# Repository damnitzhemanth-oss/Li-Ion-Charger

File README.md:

2# Li-Ion-Charger
Custom lithium ion charger that is small and does not blow up.

**The Problem** : In Indian market especially, TP4050 is available to charge lithium ion battery, but it sucks as it slowly damages the cell. But there are bigger alternatives which safely charge it. Buy those are bulky. This *Custom Li Ion charger* solves that.

# Features

1. 2A+ charging so you can charge with normal chargers.
2. Type C only.
3. Status LEDs (Red 🍒 - Charging, Green 🍏 - Charged)
4. Over Current protection with Mosfets

# BOM

| Ref | Value / Part | Description | JLCPCB Part # | Footprint | Qty | Unit Price (USD) | Total Price (USD) |
|-----|--------------|-------------|---------------|-----------|-----|------------------|-------------------|
| U1 | IP2312-4V35 | Switch-mode Li-ion charger IC, ESOP-8 | C605433 | `easyeda2kicad:ESOP-8_L4.9-W3.9-P1.27-LS6.0-BL-EP` | 1 | $0.3245 | $0.3245 |
| U2 | DW01A | Battery protection IC, SOT-23-6 | C351410 | `Package_TO_SOT_SMD:SOT-23-6` | 1 | $0.0418 | $0.0418 |
| Q1 | FS8205A | Dual N-channel MOSFET, SOT-23-6 | C55488492 | `Custom_Footprints:SOT-23-6_L2.9-W1.6-P0.95-LS2.8-BR` | 1 | $0.0483 | $0.0483 |
| L1 | 2.2 µH | Power inductor, ≥3A saturation | C515383 | `Inductor_SMD:L_0805_2012Metric` | 1 | ~$0.16 | ~$0.16 |
| C1 | 22 µF | Ceramic capacitor, input decoupling | C594231 | `Capacitor_SMD:C_0603_1608Metric` | 1 | ~$0.04 | ~$0.04 |
| C2 | 100 nF | Ceramic capacitor, DW01A bypass | C1590 | `Capacitor_SMD:C_0603_1608Metric` | 1 | ~$0.01 | ~$0.01 |
| C3 | 100 nF | Ceramic capacitor, shield bypass | C1590 | `Capacitor_SMD:C_0603_1608Metric` | 1 | ~$0.01 | ~$0.01 |
| C4 | 22 µF | Ceramic capacitor, output decoupling | C594231 | `Capacitor_SMD:C_0603_1608Metric` | 1 | ~$0.04 | ~$0.04 |
| R1 | 1 kΩ | LED current limit (Red) | C21190 | `Resistor_SMD:R_0603_1608Metric` | 1 | ~$0.01 | ~$0.01 |
| R2 | 1 kΩ | LED current limit (Green) | C21190 | `Resistor_SMD:R_0603_1608Metric` | 1 | ~$0.01 | ~$0.01 |
| R3 | 68 kΩ | ICHG set resistor (≈2A) | C25835 | `Resistor_SMD:R_0603_1608Metric` | 1 | ~$0.01 | ~$0.01 |
| R4 | 1 kΩ | CS current sense resistor | C21190 | `Resistor_SMD:R_0603_1608Metric` | 1 | ~$0.01 | ~$0.01 |
| R5 | 5.1 kΩ | CC1 pull-down | C23186 | `Resistor_SMD:R_0603_1608Metric` | 1 | ~$0.01 | ~$0.01 |
| R6 | 5.1 kΩ | CC2 pull-down | C23186 | `Resistor_SMD:R_0603_1608Metric` | 1 | ~$0.01 | ~$0.01 |
| R7 | 1 kΩ | TEST pin resistor | C21190 | `Resistor_SMD:R_0603_1608Metric` | 1 | ~$0.01 | ~$0.01 |
| R8 | 1 kΩ | VCC resistor for DW01A | C21190 | `Resistor_SMD:R_0603_1608Metric` | 1 | ~$0.01 | ~$0.01 |
| D1 | LED_RED | Charging indicator | C2286 | `LED_SMD:LED_0603_1608Metric` | 1 | ~$0.04 | ~$0.04 |
| D2 | LED_GREEN | Charge complete indicator | C72043 | `LED_SMD:LED_0603_1608Metric` | 1 | ~$0.04 | ~$0.04 |
| FB1 | Ferrite bead | 120Ω @ 100MHz, shield filter | C25415 | `Inductor_SMD:L_0603_1608Metric` | 1 | ~$0.03 | ~$0.03 |
| J1 | USB_C_Receptacle_PowerOnly_6P | USB-C power-only connector | C52209103 | `Connector_USB:USB_C_Receptacle_GCT_USB4135-GF-A_6P_TopMnt_Horizontal` | 1 | $0.2985 | $0.2985 |
| TH1 | 10 kΩ NTC | Thermistor for temperature sensing | C71322 | `Resistor_SMD:R_0603_1608Metric` | 1 | ~$0.03 | ~$0.03 |
| TP1 | TestPoint | Bat+ | N/A (PCB feature) | `TestPoint:TestPoint_Pad_D2.0mm` | 1 | $0.00 | $0.00 |
| TP2 | TestPoint | Bat− | N/A (PCB feature) | `TestPoint:TestPoint_Pad_D2.0mm` | 1 | $0.00 | $0.00 |
| TP3 | TestPoint | Out+ | N/A (PCB feature) | `TestPoint:TestPoint_Pad_D2.0mm` | 1 | $0.00 | $0.00 |
| TP4 | TestPoint | Out− | N/A (PCB feature) | `TestPoint:TestPoint_Pad_D2.0mm` | 1 | $0.00 | $0.00 |

# Schematic 

# PCB 

# Credits 
Ki Cad for PCB design, downloaded some footprints through easy eda plugin (thanks to who ever made this). And used this for compression of screenshots (made by me btw).
https://ilovefilesbyhemanth.netlify.app/

# AI Usage 
Used AI for understanding datasheets and verifying components.

# Licence

Free to use gerbers and all, but not yet tested. Feel free to modify it. but don't burn your house :)

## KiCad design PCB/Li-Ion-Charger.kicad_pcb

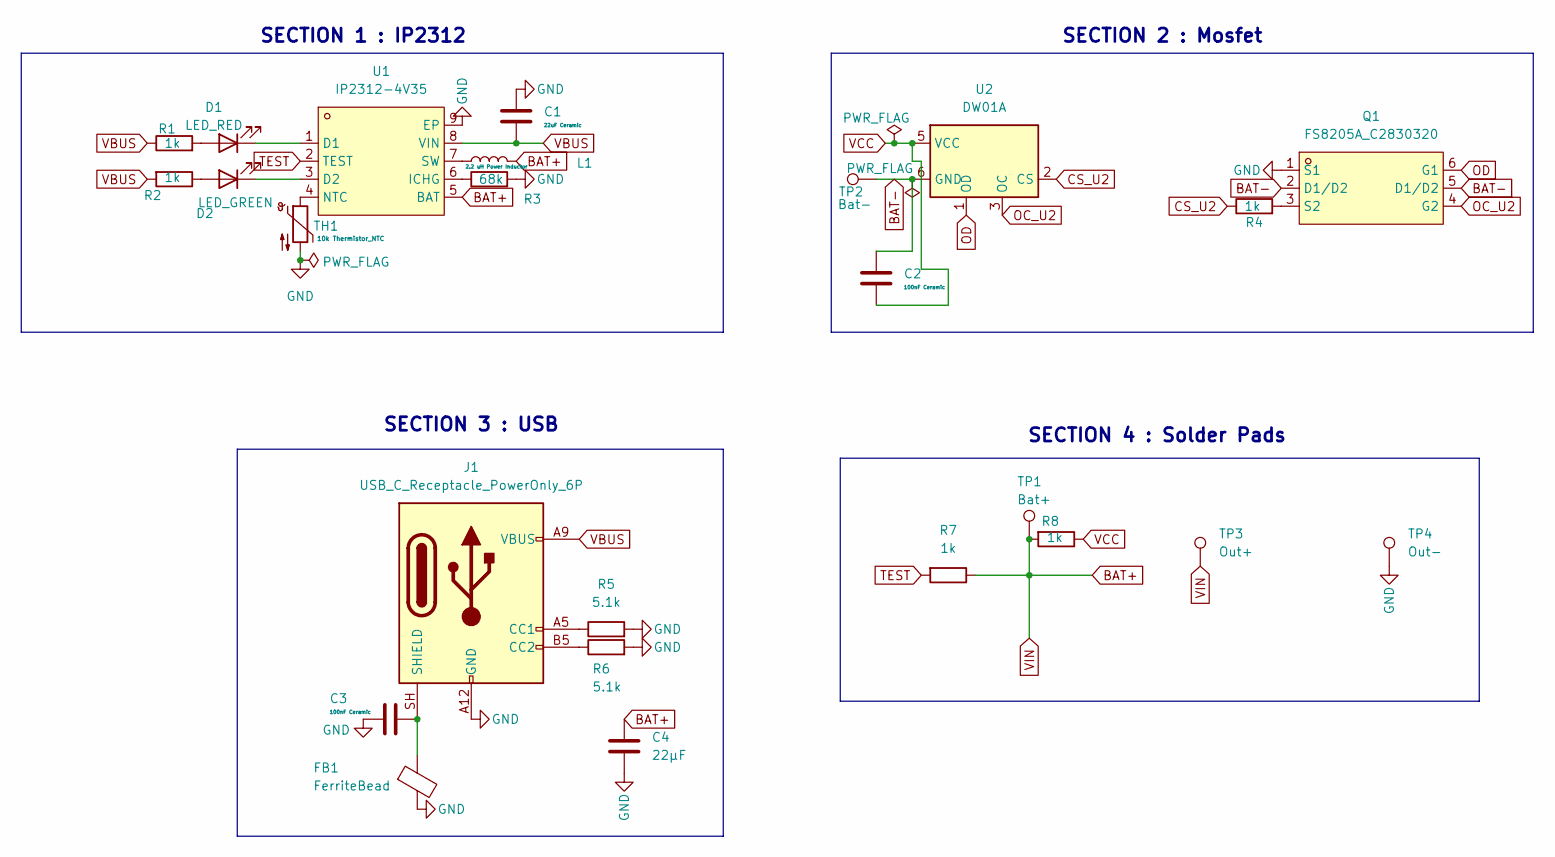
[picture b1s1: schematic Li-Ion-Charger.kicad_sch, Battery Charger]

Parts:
C1: 22uF Ceramic; C_0603_1608Metric
C2, C3: 100nF Ceramic; C_0603_1608Metric
C4: 22µF; C_0603_1608Metric
D1: LED_RED; LED_0603_1608Metric
D2: LED_GREEN; LED_0603_1608Metric
FB1: FerriteBead; L_0603_1608Metric
J1: USB_C_Receptacle_PowerOnly_6P; USB_C_Receptacle_GCT_USB4135-GF-A_6P_TopMnt_Horizontal
L1: 2.2 uH Power Inductor; L_0805_2012Metric
Q1: FS8205A_C2830320; SOT-23-6_L2.9-W1.6-P0.95-LS2.8-BR; MPN FS8205A; LCSC Part C2830320
R1, R2, R4, R7, R8: 1k; R_0603_1608Metric
R3: 68k; R_0603_1608Metric
R5, R6: 5.1k; R_0603_1608Metric
TH1: 10k Thermistor_NTC; R_0603_1608Metric
TP1: Bat+; TestPoint_Pad_D2.0mm
TP2: Bat-; TestPoint_Pad_D2.0mm
TP3: Out+; TestPoint_Pad_D2.0mm
TP4: Out-; TestPoint_Pad_D2.0mm
U1: IP2312-4V35; ESOP-8_L4.9-W3.9-P1.27-LS6.0-BL-EP; MPN IP2312-4V35; LCSC Part C605433
U2: DW01A; SOT-23-6

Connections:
BAT+: C4.1, L1.2, R7.1, R8.2, TP1.1 (1_1), TP3.1 (1_1), U1.5 (BAT)
BAT-: C2.1, Q1.2 (D1/D2), Q1.5 (D1/D2), TP2.1 (1_1), U2.6 (GND)
CS_U2: R4.1, U2.2 (CS)
GND: C1.1, C3.2, C4.2, FB1.2, J1.A12 (GND), J1.B12 (GND), Q1.1 (S1), R3.2, R5.2, R6.2, TH1.2, TP4.1 (1_1), U1.9 (EP)
unnamed: D1.2 (A), R1.2
unnamed: D1.1 (K), U1.1 (D1)
unnamed: D2.2 (A), R2.1
unnamed: D2.1 (K), U1.3 (D2)
unnamed: J1.A5 (CC1), R5.1
unnamed: J1.B5 (CC2), R6.1
unnamed: C3.1, FB1.1, J1.SH (SHIELD)
unnamed: Q1.3 (S2), R4.2
unnamed: R3.1, U1.6 (ICHG)
unnamed: TH1.1, U1.4 (NTC)
unnamed: L1.1, U1.7 (SW)
OC_U2: Q1.4 (G2), U2.3 (OC)
OD: Q1.6 (G1), U2.1 (OD)
TEST: R7.2, U1.2 (TEST)
VBUS: C1.2, J1.A9 (VBUS), J1.B9 (VBUS), R1.1, R2.2, U1.8 (VIN)
VCC: C2.2, R8.1, U2.5 (VCC)

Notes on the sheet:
SECTION 3 : USB
SECTION 4 : Solder Pads
SECTION 2 : Mosfet
SECTION 1 : IP2312

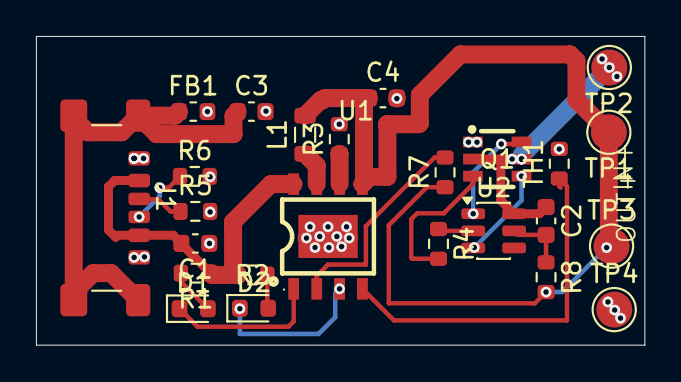
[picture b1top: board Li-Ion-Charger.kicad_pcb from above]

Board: 2 copper layers, 33.8 x 17.1 mm, 25 parts (0 on the bottom side), 20 nets.

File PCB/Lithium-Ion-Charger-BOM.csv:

| Ref | Value / Part | Description | JLCPCB Part # | Footprint | Qty | Unit Price (USD) | Total Price (USD) |
|-----|--------------|-------------|---------------|-----------|-----|------------------|-------------------|
| U1 | IP2312-4V35 | Switch-mode Li-ion charger IC, ESOP-8 | C605433 | `easyeda2kicad:ESOP-8_L4.9-W3.9-P1.27-LS6.0-BL-EP` | 1 | $0.3245 | $0.3245 |
| U2 | DW01A | Battery protection IC, SOT-23-6 | C351410 | `Package_TO_SOT_SMD:SOT-23-6` | 1 | $0.0418 | $0.0418 |
| Q1 | FS8205A | Dual N-channel MOSFET, SOT-23-6 | C55488492 | `Custom_Footprints:SOT-23-6_L2.9-W1.6-P0.95-LS2.8-BR` | 1 | $0.0483 | $0.0483 |
| L1 | 2.2 µH | Power inductor, ≥3A saturation | C515383 | `Inductor_SMD:L_0805_2012Metric` | 1 | ~$0.16 | ~$0.16 |
| C1 | 22 µF | Ceramic capacitor, input decoupling | C594231 | `Capacitor_SMD:C_0603_1608Metric` | 1 | ~$0.04 | ~$0.04 |
| C2 | 100 nF | Ceramic capacitor, DW01A bypass | C1590 | `Capacitor_SMD:C_0603_1608Metric` | 1 | ~$0.01 | ~$0.01 |
| C3 | 100 nF | Ceramic capacitor, shield bypass | C1590 | `Capacitor_SMD:C_0603_1608Metric` | 1 | ~$0.01 | ~$0.01 |
| C4 | 22 µF | Ceramic capacitor, output decoupling | C594231 | `Capacitor_SMD:C_0603_1608Metric` | 1 | ~$0.04 | ~$0.04 |
| R1 | 1 kΩ | LED current limit (Red) | C21190 | `Resistor_SMD:R_0603_1608Metric` | 1 | ~$0.01 | ~$0.01 |
| R2 | 1 kΩ | LED current limit (Green) | C21190 | `Resistor_SMD:R_0603_1608Metric` | 1 | ~$0.01 | ~$0.01 |
| R3 | 68 kΩ | ICHG set resistor (≈2A) | C25835 | `Resistor_SMD:R_0603_1608Metric` | 1 | ~$0.01 | ~$0.01 |
| R4 | 1 kΩ | CS current sense resistor | C21190 | `Resistor_SMD:R_0603_1608Metric` | 1 | ~$0.01 | ~$0.01 |
| R5 | 5.1 kΩ | CC1 pull-down | C23186 | `Resistor_SMD:R_0603_1608Metric` | 1 | ~$0.01 | ~$0.01 |
| R6 | 5.1 kΩ | CC2 pull-down | C23186 | `Resistor_SMD:R_0603_1608Metric` | 1 | ~$0.01 | ~$0.01 |
| R7 | 1 kΩ | TEST pin resistor | C21190 | `Resistor_SMD:R_0603_1608Metric` | 1 | ~$0.01 | ~$0.01 |
| R8 | 1 kΩ | VCC resistor for DW01A | C21190 | `Resistor_SMD:R_0603_1608Metric` | 1 | ~$0.01 | ~$0.01 |
| D1 | LED_RED | Charging indicator | C2286 | `LED_SMD:LED_0603_1608Metric` | 1 | ~$0.04 | ~$0.04 |
| D2 | LED_GREEN | Charge complete indicator | C72043 | `LED_SMD:LED_0603_1608Metric` | 1 | ~$0.04 | ~$0.04 |
| FB1 | Ferrite bead | 120Ω @ 100MHz, shield filter | C25415 | `Inductor_SMD:L_0603_1608Metric` | 1 | ~$0.03 | ~$0.03 |
| J1 | USB_C_Receptacle_PowerOnly_6P | USB-C power-only connector | C52209103 | `Connector_USB:USB_C_Receptacle_GCT_USB4135-GF-A_6P_TopMnt_Horizontal` | 1 | $0.2985 | $0.2985 |
| TH1 | 10 kΩ NTC | Thermistor for temperature sensing | C71322 | `Resistor_SMD:R_0603_1608Metric` | 1 | ~$0.03 | ~$0.03 |
| TP1 | TestPoint | Bat+ | N/A (PCB feature) | `TestPoint:TestPoint_Pad_D2.0mm` | 1 | $0.00 | $0.00 |
| TP2 | TestPoint | Bat− | N/A (PCB feature) | `TestPoint:TestPoint_Pad_D2.0mm` | 1 | $0.00 | $0.00 |
| TP3 | TestPoint | Out+ | N/A (PCB feature) | `TestPoint:TestPoint_Pad_D2.0mm` | 1 | $0.00 | $0.00 |
| TP4 | TestPoint | Out− | N/A (PCB feature) | `TestPoint:TestPoint_Pad_D2.0mm` | 1 | $0.00 | $0.00 |
